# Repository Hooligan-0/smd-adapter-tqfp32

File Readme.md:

SMD adapter for TQFP32 packages
===============================

This project is a small smd-to-pin adapter for TQFP-32 packages. His goal is to
help using smd ic components during prototyping of electronic boards.

CAD sources
-----------

This board has been designed using KiCad EDA (version 7). All sources files
(schematics, routing, ...) are available into the `prj-kicad` folder.

License
-------

This project is OpenHardware. All materials are published and can be used
under terms of the CERN-OHL-S v2 license (see License.txt).

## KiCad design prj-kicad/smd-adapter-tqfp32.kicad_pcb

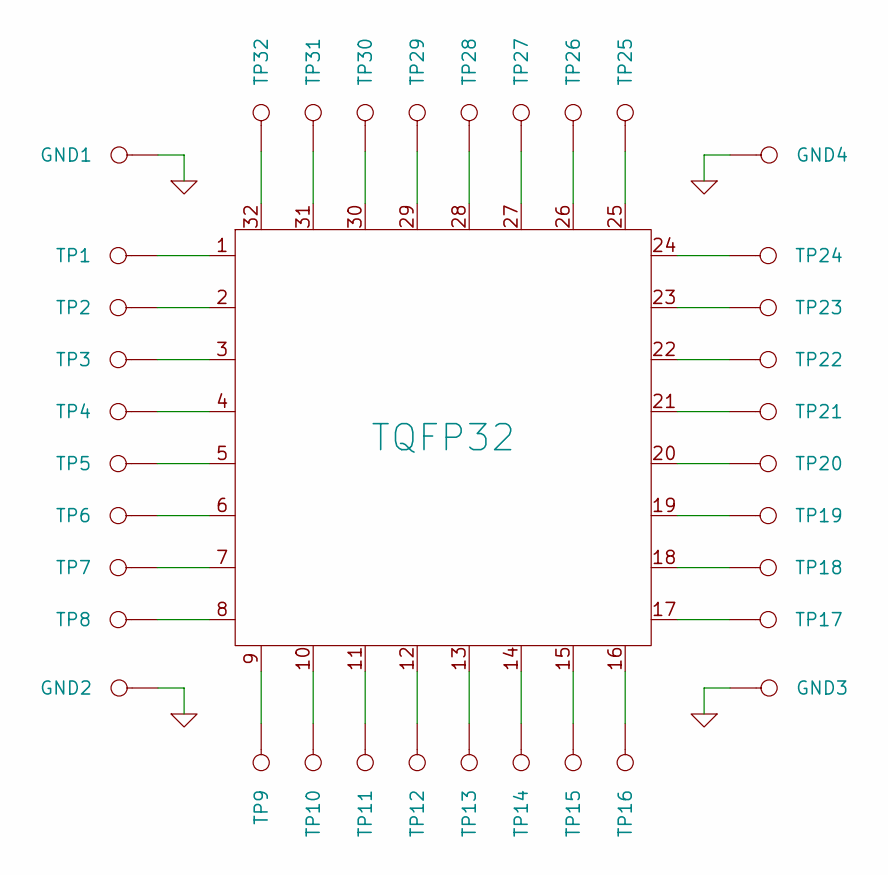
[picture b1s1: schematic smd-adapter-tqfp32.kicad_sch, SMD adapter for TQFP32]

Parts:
GND1, GND2, GND3, GND4: CONN_1; TP_SQ
TP1, TP2, TP3, TP4, TP5, TP6, TP7, TP8, TP9, TP10, TP11, TP12, TP13, TP14, TP15, TP16, TP17, TP18, TP19, TP20, TP21, TP22, TP23, TP24, TP25, TP26, TP27, TP28, TP29, TP30, TP31, TP32: CONN_1; TP
TQFP32: TQFP32

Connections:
GND: GND1.1, GND2.1, GND3.1, GND4.1
unnamed: TP1.1, TQFP32.1
unnamed: TP2.1, TQFP32.2
unnamed: TP3.1, TQFP32.3
unnamed: TP4.1, TQFP32.4
unnamed: TP5.1, TQFP32.5
unnamed: TP6.1, TQFP32.6
unnamed: TP7.1, TQFP32.7
unnamed: TP8.1, TQFP32.8
unnamed: TP9.1, TQFP32.9
unnamed: TP10.1, TQFP32.10
unnamed: TP11.1, TQFP32.11
unnamed: TP12.1, TQFP32.12
unnamed: TP13.1, TQFP32.13
unnamed: TP14.1, TQFP32.14
unnamed: TP15.1, TQFP32.15
unnamed: TP16.1, TQFP32.16
unnamed: TP17.1, TQFP32.17
unnamed: TP18.1, TQFP32.18
unnamed: TP19.1, TQFP32.19
unnamed: TP20.1, TQFP32.20
unnamed: TP21.1, TQFP32.21
unnamed: TP22.1, TQFP32.22
unnamed: TP23.1, TQFP32.23
unnamed: TP24.1, TQFP32.24
unnamed: TP25.1, TQFP32.25
unnamed: TP26.1, TQFP32.26
unnamed: TP27.1, TQFP32.27
unnamed: TP28.1, TQFP32.28
unnamed: TP29.1, TQFP32.29
unnamed: TP30.1, TQFP32.30
unnamed: TP31.1, TQFP32.31
unnamed: TP32.1, TQFP32.32

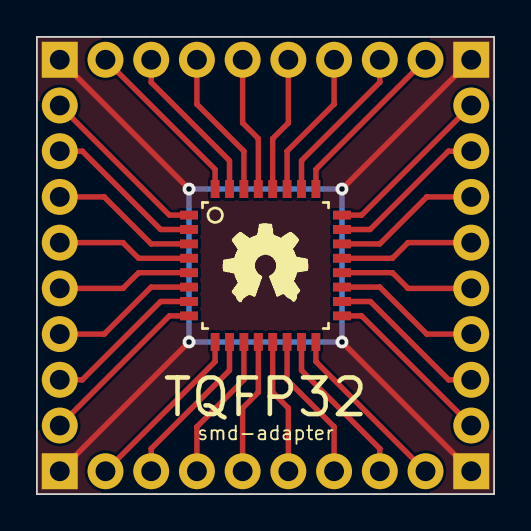
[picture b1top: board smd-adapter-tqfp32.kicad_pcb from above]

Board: 2 copper layers, 25.4 x 25.4 mm, 38 parts (0 on the bottom side), 33 nets.

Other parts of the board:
ohw_logo: VAL**; logo-ohw

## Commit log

2024-10-06 --=={ Create project }==--

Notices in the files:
prj-kicad/smd-adapter-tqfp32.kicad_pcb:
License: CERN-OHL-S v 2
